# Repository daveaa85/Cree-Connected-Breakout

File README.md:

# Cree-Connected-Breakout

Overview:
  This is an Eagle CAD project to make a power/interface PCB for the Cree Connected RF board. This facilitates usage of the low cost Cree LED to interface to other hardware. Open collector transistor drive allow drive of relays or drive of different voltage level H/W interfaces.
  
-- RF module description --
Inside the A19 Cree Connected LED is an add on PCB which implements the ZigBee radio function.
The PCB is attached to the main LED power supply with a 4 pin connector having a 2mm pitch.

---- RF Board connector pins --
Pin 1 - Gnd
Pin 2 - +3v
Pin 3 - PWM
Pin 4 - On, /Off

-- Features --
1) USB micro connector provides +5v supply
2) 3.3v/800mA regulator can supply external hardware via output connector
3) Cree RF board PWM and On/Off signals are buffered by open collector transistor drive
4) Solder pad selectable +5v/3.3v power supply output for external system use.

-- Parts list --
1) PCB - Interface
2) 0.1uf bypass cap - body size 1206, quantity = 2, C1, C2
3) MUN2212 pre-biased NPM transistor, quantity = 2, Q1, Q2
4) Low Dropout regulator, AP7363-33D-13 3.3v/1.5A , 3.3v, package SOT-23, U1
5) JST-PTH series 4 pin 2.0mm vertical connector J1
6) Cree Connected RF module - remove from Cree Connected LED.

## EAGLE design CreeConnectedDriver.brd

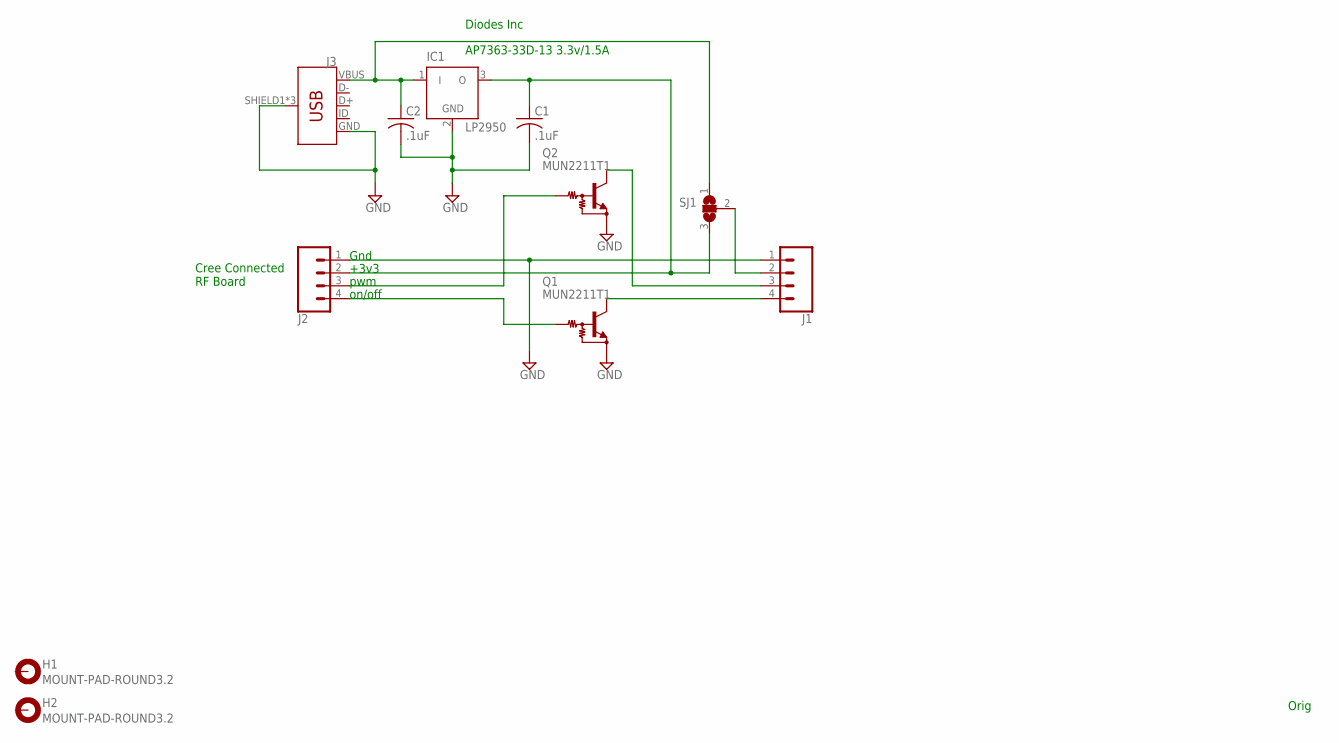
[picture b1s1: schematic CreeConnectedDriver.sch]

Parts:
C1, C2: .1uF; C1206
H1, H2: MOUNT-PAD-ROUND3.2; 3,2-PAD
IC1: LP2950; DPACK
J1, J2: CONN_04JST-PTH-VERT; JST-4-PTH-VERT
J3: USB_MICRO-B_FEMALE-SMT; USB-B-MICRO-SMD
Q1, Q2: MUN2211T1; SC59-BEC
SJ1: SJ2W; SJ_2

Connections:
GND: C1.2, C2.2, IC1.2 (GND), J1.1, J2.1, J3.GND, J3.SHIELD1 (SHIELD), J3.SHIELD2 (SHIELD), J3.SHIELD3 (SHIELD), Q1.E, Q2.E
unnamed: C1.1, IC1.3 (O), J2.2, SJ1.3
unnamed: J1.2, SJ1.2
unnamed: J2.3, Q2.B
unnamed: J2.4, Q1.B
unnamed: J1.4, Q1.C
unnamed: J1.3, Q2.C
unnamed: C2.1, IC1.1 (I), J3.VBUS, SJ1.1

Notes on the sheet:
Gnd
+3v3
pwm
on/off
Orig
Cree Connected RF Board
AP7363-33D-13 3.3v/1.5A
Diodes Inc

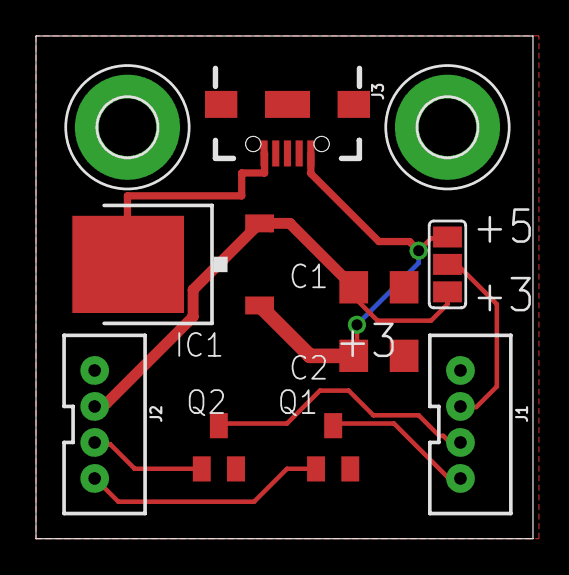
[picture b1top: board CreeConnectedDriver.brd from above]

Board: 2 copper layers, 27.6 x 27.9 mm, 11 parts (0 on the bottom side), 8 nets.

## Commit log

2017-04-15 Update README.md
    Initial version

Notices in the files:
parts and their libraries:
SparkFun-Connectors: Licensing: Creative Commons ShareAlike 4.0 International - https://creativecommons.org/licenses/by-sa/4.0
